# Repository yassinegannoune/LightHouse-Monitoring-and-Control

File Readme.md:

# **Lighthouse - IoT Monitoring System for Lighthouse State**

### **Overview**
The *Lighthouse* project is an IoT-based system designed to monitor and control the state of the Al Hank lighthouse in Casablanca. This system integrates a custom electronic board with sensors and communication modules to monitor parameters such as power supply status, lighting functionality, and environmental conditions. LTE cellular communication and the MQTT protocol are used to transmit real-time data to the ThingsBoard platform for remote monitoring and control. Additionally, an alarm notification system triggers alerts to designated personnel when issues are detected, ensuring timely intervention.

### **Project Details**
- **Platform**: ThingsBoard (Cloud version)
- **Communication Protocol**: MQTT (Message Queuing Telemetry Transport) for data efficiency
- **Network**: LTE (Long-Term Evolution) for reliable, wide-range connectivity
- **Alarm Notification**: The system includes an alarm feature that sends notifications via ThingsBoard when anomalies or malfunctions are detected.
  
### **Objectives**
The project aims to provide a cost-effective and reliable solution to remotely monitor and control lighthouse functionality, minimizing the need for manual intervention and ensuring maritime safety. The primary goals are to:
1. Automate the lighthouse monitoring process and reduce dependency on human intervention.
2. Develop a custom PCB with optimized impedance and reduced electromagnetic interference (crosstalk).
3. Implement a firmware solution for real-time data collection, processing, and MQTT-based communication.
4. Enable remote control functionality through ThingsBoard for seamless adjustments and troubleshooting.
5. Integrate an alarm notification system to respond promptly to malfunctions.

### **Project Components and Hardware Design**
1. **Sensor Integration**  
   - Sensors used include capacitive proximity sensors (to detect rotation frequency), light-dependent resistors (LDR) for lighting functionality, and optional environmental sensors like temperature and humidity.
  
2. **Custom PCB Design**  
   - The custom PCB is designed with multiple layers for effective power management, using components like the ATmega2560 microcontroller and SIM808 module for cellular communication. Voltage regulation and design practices, such as minimizing crosstalk and optimizing impedance, were critical to PCB stability.
  
3. **LTE and MQTT Communication**  
   - The SIM808 module facilitates LTE cellular communication. MQTT is used due to its low bandwidth and efficient publish-subscribe model, which is well-suited for IoT applications.

4. **ThingsBoard Platform**  
   - Data is sent to ThingsBoard, which acts as the central monitoring and control hub. MQTT data is formatted in JSON and transmitted under specific topics to ThingsBoard, allowing for seamless integration.
    
5. **Alarm Notification System**  
   - The alarm system is configured within ThingsBoard to alert operators via email when critical thresholds or malfunctions are detected, ensuring rapid response.

### **Project Phases**
The project is structured into distinct phases following a V-model lifecycle:
1. **Requirements & Planning**  
   - A detailed analysis was performed, and a benchmark study was conducted to determine suitable hardware and protocols.

2. **Design & Prototyping**  
   - The hardware architecture includes multiple functional blocks, such as power regulation, microcontroller, sensors, and LTE communication. The PCB was designed to ensure stability and efficiency, incorporating multilayer structures to manage impedance.

3. **Firmware Development**  
   - Firmware was developed in C, utilizing AT commands for SIM808 configuration and MQTT for data handling. Functions include sensor data acquisition, processing, and communication with ThingsBoard.

4. **Testing & Validation**  
   - The system underwent tests for communication stability, sensor accuracy, and alarm functionality, ensuring reliability and efficiency under different scenarios.

5. **Deployment**  
   - The final implementation involved deploying the PCB and connecting it to ThingsBoard, enabling live monitoring and control of the lighthouse.

### **Getting Started**
To begin with the *Lighthouse* project, you will need:
- LTE-enabled development board and sensors.
- A ThingsBoard account for monitoring and control.
- A development environment for firmware and MQTT setup.

### **Setup Instructions**
1. **Clone the Repository**:  
   ```bash
   git clone https://github.com/yassinegannoune/LightHouse-Monitoring-and-Control.git)
   
2. **Install Dependencies**:
   - Install required libraries for sensor interfacing, LTE communication, and MQTT protocol.

3. **Configure MQTT & LTE**:
   - Set up MQTT credentials and LTE configuration for ThingsBoard.

4. **Run Tests**:
   - Test firmware functionality on the development board, ensuring accurate data transmission to ThingsBoard.

### **License**
This project is licensed under the MIT License - see the LICENSE file for details.

### **Contact**
For further inquiries, contact [yassine.gannoune@usmba.ac.ma] or open an issue on the project repository.

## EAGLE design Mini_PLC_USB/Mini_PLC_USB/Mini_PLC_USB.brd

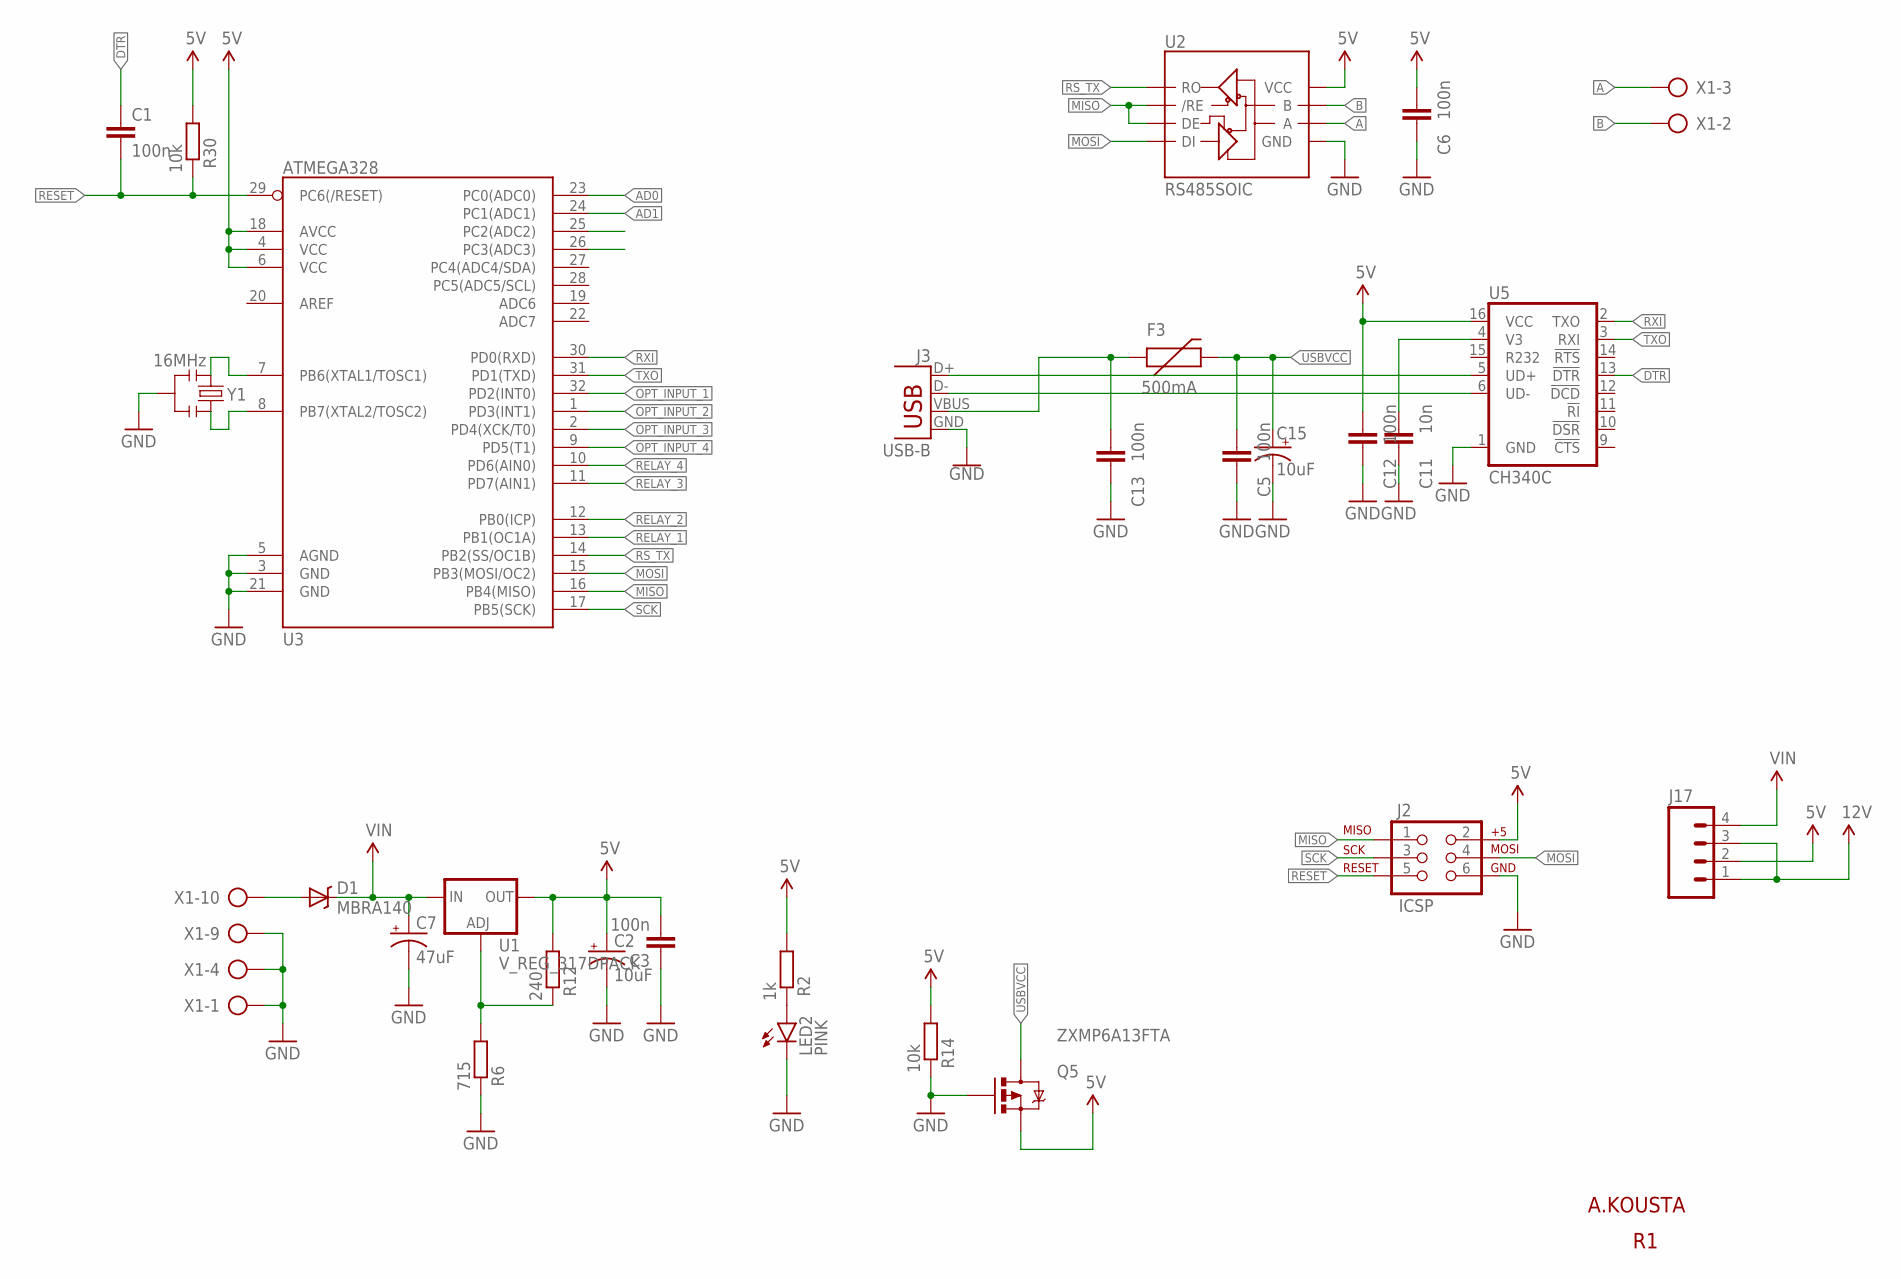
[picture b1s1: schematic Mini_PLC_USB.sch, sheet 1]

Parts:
C1, C3, C5, C6, C12, C13: 100n; C1206
C2, C15: 10uF; EIA3216
C7: 47uF; PANASONIC_D; MPN EEE1CA470SP
C11: 10n; C1206
D1: MBRA140; SMA-DIODE; MPN B140-13-F
F3: 500mA; PTC-1206
J2: ICSP; 2X3
J3: USB-B; USB-B-PTH; MPN USB-B-S-RA
J17: M04PTH; 1X04
LED2: PINK; LED-1206@1
Q5: ZXMP6A13FTA; SOT23-3; MPN ZXMP6A13FTA
R2: 1k; M1206
R6: 715; M1206
R12: 240; M1206
R14, R30: 10k; M1206
U1: V_REG_317DPACK; V-REG_DPACK
U2: RS485SOIC; SO08
U3: ATMEGA328; TQFP32-08
U5: CH340C; SO016
X1: AK500/10-H
Y1: 16MHz; RESONATOR-SMD

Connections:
5V: C2.A (+), C3.2, C6.2, C12.2, J2.2, J17.2, Q5.2 (S), R2.1, R12.1, R14.1, R30.1, U1.4 (OUT), U2.8 (VCC), U3.4 (VCC), U3.6 (VCC), U3.18 (AVCC), U5.16 (VCC); also elsewhere on the board
12V: J17.1, J17.3; also elsewhere on the board
A: U2.6 (A), X1.3
AD0: U3.23 (PC0(ADC0))
AD1: U3.24 (PC1(ADC1))
B: U2.7 (B), X1.2
D+: J3.D+, U5.5 (UD+)
D-: J3.D-, U5.6 (UD-)
DTR: C1.1, U5.13 (!DTR)
GND: C2.C (-), C3.1, C5.1, C6.1, C7.-, C11.1, C12.1, C13.1, C15.-, J2.6, J3.GND, LED2.C, Q5.1 (G), R6.2, R14.2, U2.5 (GND), U3.3 (GND), U3.5 (AGND), U3.21 (GND), U5.1 (GND), X1.1, X1.4, X1.9, Y1.2; also elsewhere on the board
MISO: J2.1, U2.2 (/RE), U2.3 (DE), U3.16 (PB4(MISO))
MOSI: J2.4, U2.4 (DI), U3.15 (PB3(MOSI/OC2))
unnamed: LED2.A, R2.2
unnamed: U3.7 (PB6(XTAL1/TOSC1)), Y1.1
unnamed: R6.1, R12.2, U1.1 (ADJ)
unnamed: U3.8 (PB7(XTAL2/TOSC2)), Y1.3
unnamed: D1.A, X1.10
unnamed: C11.2, U5.4 (V3)
OPT_INPUT_1: U3.32 (PD2(INT0)); also elsewhere on the board
OPT_INPUT_2: U3.1 (PD3(INT1)); also elsewhere on the board
OPT_INPUT_3: U3.2 (PD4(XCK/T0)); also elsewhere on the board
OPT_INPUT_4: U3.9 (PD5(T1)); also elsewhere on the board
RELAY_1: U3.13 (PB1(OC1A)); also elsewhere on the board
RELAY_2: U3.12 (PB0(ICP)); also elsewhere on the board
RELAY_3: U3.11 (PD7(AIN1)); also elsewhere on the board
RELAY_4: U3.10 (PD6(AIN0)); also elsewhere on the board
RESET: C1.2, J2.5, R30.2, U3.29 (PC6(/RESET))
RS_TX: U2.1 (RO), U3.14 (PB2(SS/OC1B))
RXI: U3.30 (PD0(RXD)), U5.2 (TXO)
SCK: J2.3, U3.17 (PB5(SCK))
TXO: U3.31 (PD1(TXD)), U5.3 (RXI)
USBVCC: C5.2, C15.+, F3.2, Q5.3 (D)
VIN: C7.+, D1.C, J17.4, U1.3 (IN); also elsewhere on the board
VUSB: C13.2, F3.1, J3.VBUS

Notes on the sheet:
A.KOUSTA

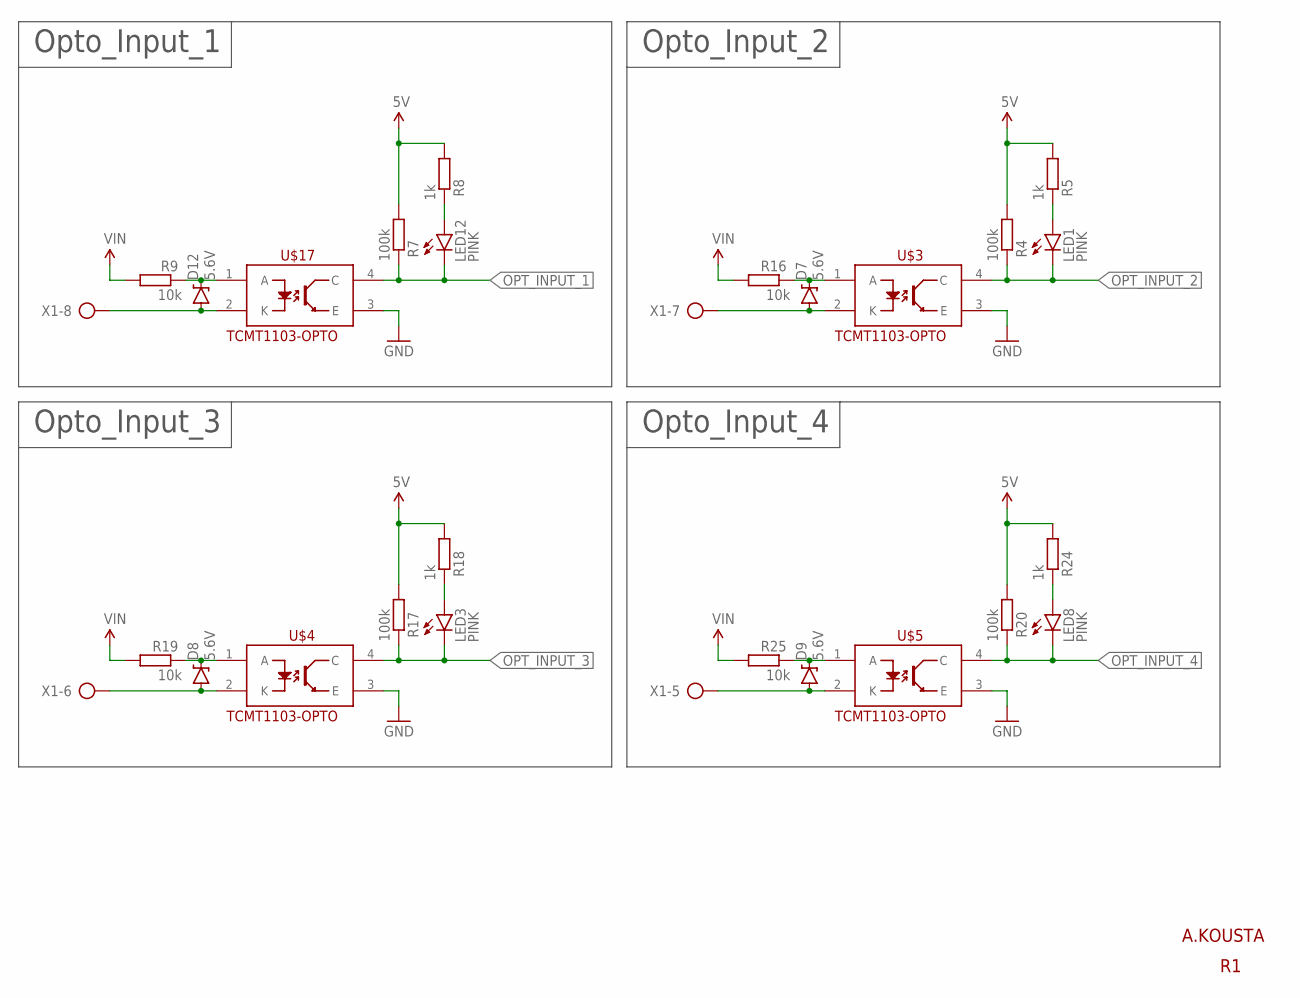
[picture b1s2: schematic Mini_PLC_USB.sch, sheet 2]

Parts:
D7, D8, D9, D12: 5.6V; SOD-323
LED1, LED3, LED8, LED12: PINK; LED-1206@1
R4, R7, R17, R20: 100k; M1206
R5, R8, R18, R24: 1k; M1206
R9, R16, R19, R25: 10k; M1206
U$3, U$4, U$5, U$17: TCMT1103-OPTO; SSOP-4
X1: AK500/10-H

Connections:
5V: R4.1, R5.1, R7.1, R8.1, R17.1, R18.1, R20.1, R24.1; also elsewhere on the board
GND: U$3.3 (E), U$4.3 (E), U$5.3 (E), U$17.3 (E); also elsewhere on the board
unnamed: D12.A, U$17.2 (K), X1.8
unnamed: D12.C, R9.2, U$17.1 (A)
unnamed: D7.C, R16.2, U$3.1 (A)
unnamed: D7.A, U$3.2 (K), X1.7
unnamed: LED1.A, R5.2
unnamed: D8.C, R19.2, U$4.1 (A)
unnamed: D8.A, U$4.2 (K), X1.6
unnamed: LED3.A, R18.2
unnamed: D9.C, R25.2, U$5.1 (A)
unnamed: D9.A, U$5.2 (K), X1.5
unnamed: LED8.A, R24.2
unnamed: LED12.A, R8.2
OPT_INPUT_1: LED12.C, R7.2, U$17.4 (C); also elsewhere on the board
OPT_INPUT_2: LED1.C, R4.2, U$3.4 (C); also elsewhere on the board
OPT_INPUT_3: LED3.C, R17.2, U$4.4 (C); also elsewhere on the board
OPT_INPUT_4: LED8.C, R20.2, U$5.4 (C); also elsewhere on the board
VIN: R9.1, R16.1, R19.1, R25.1; also elsewhere on the board

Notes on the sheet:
Opto_Input_1
Opto_Input_2
Opto_Input_3
Opto_Input_4
A.KOUSTA

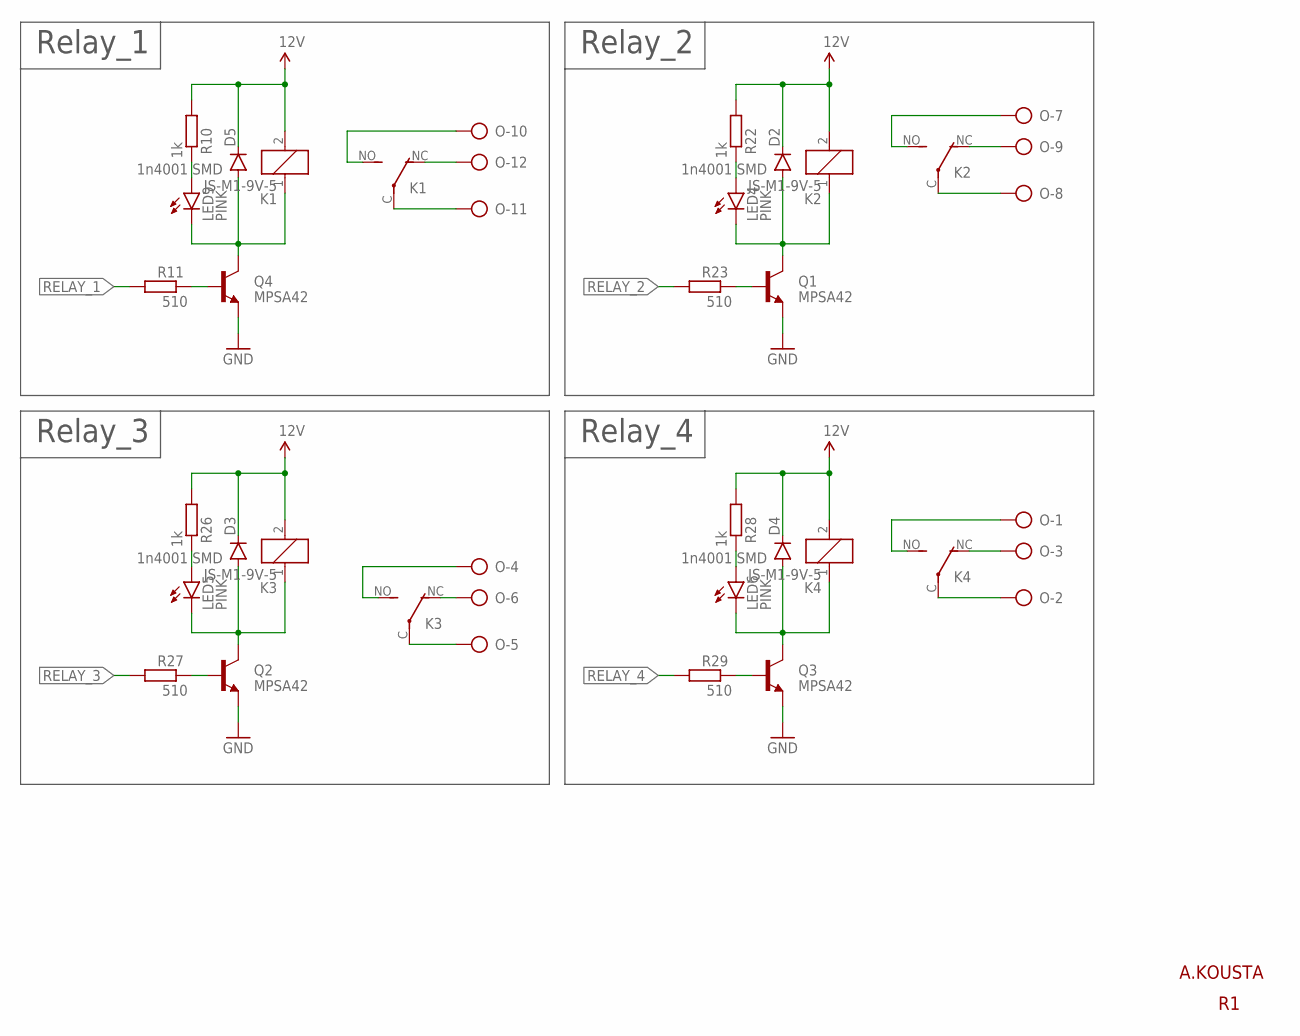
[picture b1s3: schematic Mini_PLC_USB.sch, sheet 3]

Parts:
D2, D3, D4, D5: 1n4001 SMD; SOD-123
K1, K2, K3, K4: JS-M1-9V-5; JS-M
LED4, LED5, LED6, LED9: PINK; LED-1206@1
O: AK500/12-H
Q1, Q2, Q3, Q4: MPSA42; SOT23-3@1
R10, R22, R26, R28: 1k; M1206
R11, R23, R27, R29: 510; M1206

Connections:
12V: D2.C, D3.C, D4.C, D5.C, K1.2, K2.2, K3.2, K4.2, R10.1, R22.1, R26.1, R28.1; also elsewhere on the board
GND: Q1.2 (E), Q2.2 (E), Q3.2 (E), Q4.2 (E); also elsewhere on the board
unnamed: D2.A, K2.1, LED4.C, Q1.3 (C)
unnamed: Q1.1 (B), R23.2
unnamed: LED4.A, R22.2
unnamed: D5.A, K1.1, LED9.C, Q4.3 (C)
unnamed: LED9.A, R10.2
unnamed: D3.A, K3.1, LED5.C, Q2.3 (C)
unnamed: Q4.1 (B), R11.2
unnamed: Q2.1 (B), R27.2
unnamed: LED5.A, R26.2
unnamed: K1.C, O.11
unnamed: K1.NC (O), O.12
unnamed: K1.NO (S), O.10
unnamed: D4.A, K4.1, LED6.C, Q3.3 (C)
unnamed: Q3.1 (B), R29.2
unnamed: K2.C, O.8
unnamed: K2.NC (O), O.9
unnamed: K2.NO (S), O.7
unnamed: LED6.A, R28.2
unnamed: K3.C, O.5
unnamed: K3.NC (O), O.6
unnamed: K3.NO (S), O.4
unnamed: K4.C, O.2
unnamed: K4.NC (O), O.3
unnamed: K4.NO (S), O.1
RELAY_1: R11.1; also elsewhere on the board
RELAY_2: R23.1; also elsewhere on the board
RELAY_3: R27.1; also elsewhere on the board
RELAY_4: R29.1; also elsewhere on the board

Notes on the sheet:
Relay_1
Relay_2
Relay_3
Relay_4
A.KOUSTA

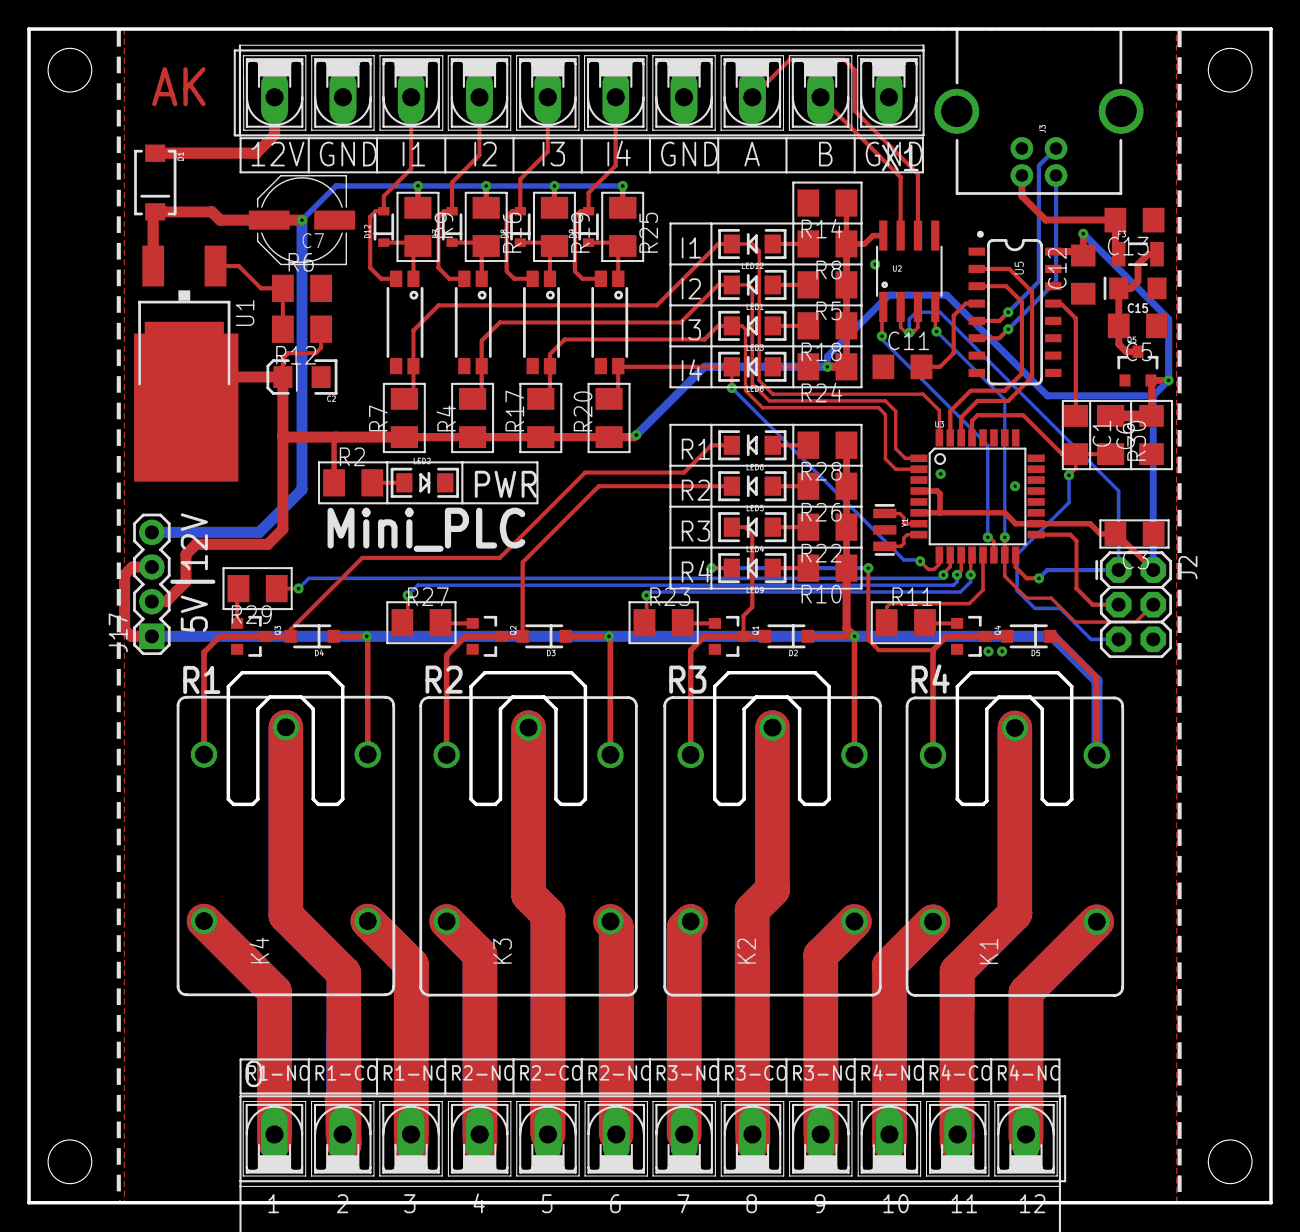
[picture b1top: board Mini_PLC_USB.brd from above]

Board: 2 copper layers, 90.9 x 85.9 mm, 77 parts (0 on the bottom side), 68 nets.

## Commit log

2024-11-15 lighthouse commits

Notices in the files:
parts and their libraries:
SparkFun-Connectors: Licensing: CC v3.0 Share-Alike You are welcome to use this library for commercial purposes.
SparkFun-PowerIC: Licensing: Creative Commons ShareAlike 4.0 International - https://creativecommons.org/licenses/by-sa/4.0
